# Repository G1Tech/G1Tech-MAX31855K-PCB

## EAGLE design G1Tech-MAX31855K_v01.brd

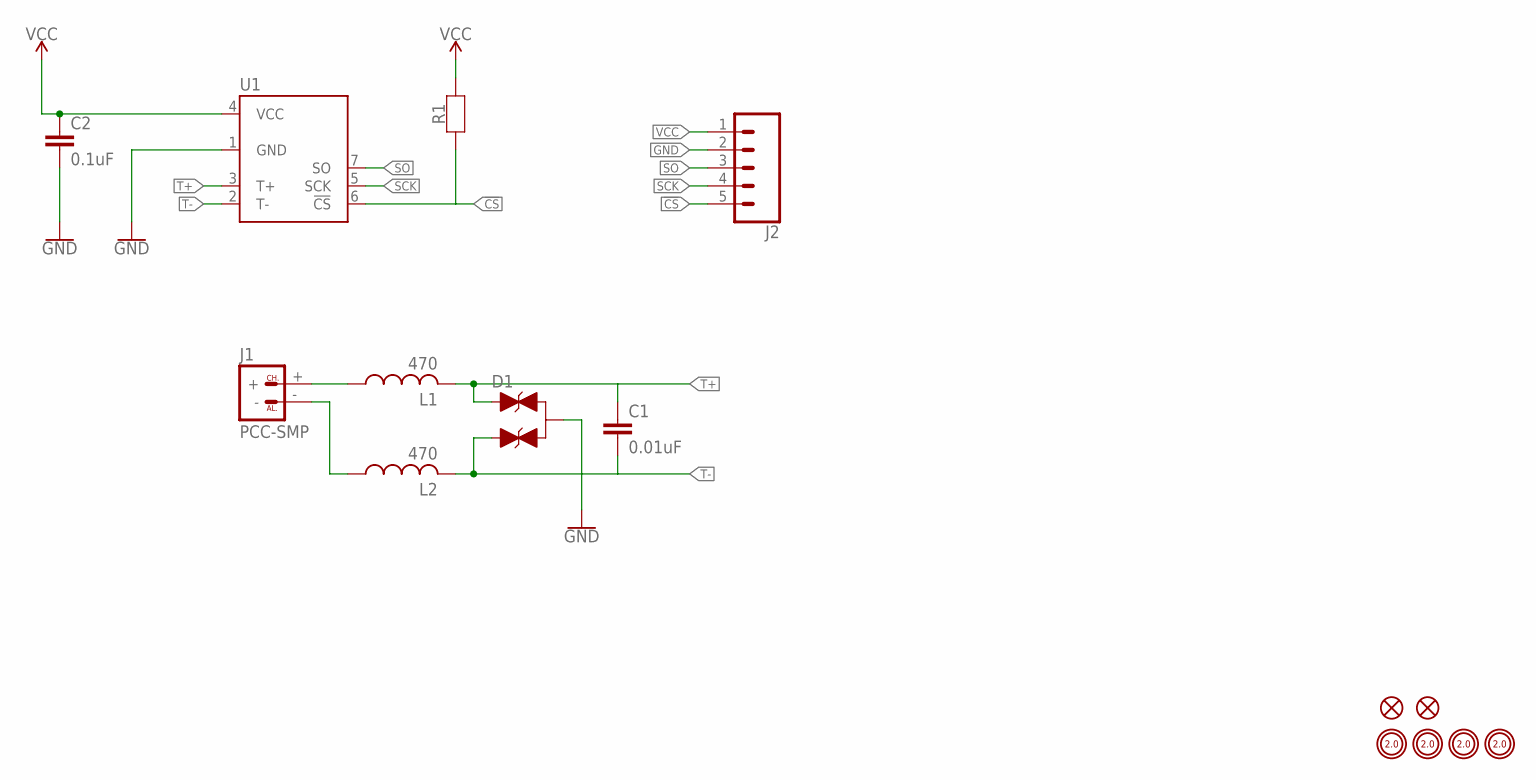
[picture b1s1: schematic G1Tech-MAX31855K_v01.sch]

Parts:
C1: 0.01uF; C0603
C2: 0.1uF; C0603
D1: DIODE-TVS-NUP2105L; SOT23-3
FD1, FD2: FIDUCIAL-1X2
H1, H2, H3, H4: MOUNTINGHOLE-PLATED-2.0
J1: PCC-SMP
J2: CONN-1X5; 1X05_NO_SILK
L1, L2: 470; MURATA-L0603
R1: YAGEO-R0603
U1: MAX31855KASA+; SO08

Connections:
!CS: J2.5, R1.1, U1.6 (!CS)
GND: C2.2, D1.3, J2.2, U1.1 (GND)
unnamed: J1.+, L1.1
unnamed: J1.-, L2.1
SCK: J2.4, U1.5 (SCK)
SO: J2.3, U1.7 (SO)
T+: C1.1, D1.1, L1.2, U1.3 (T+)
T-: C1.2, D1.2, L2.2, U1.2 (T-)
VCC: C2.1, J2.1, R1.2, U1.4 (VCC)

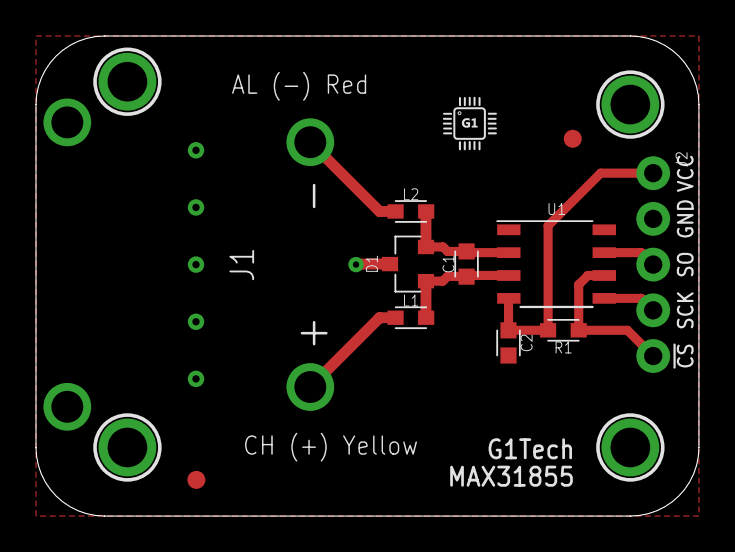
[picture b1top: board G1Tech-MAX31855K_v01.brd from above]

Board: 2 copper layers, 36.8 x 26.7 mm, 17 parts (1 on the bottom side), 9 nets.

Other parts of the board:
U$1: LOGO-G1TECH-5MM
U$2: LOGO-G1TECH-3MM
